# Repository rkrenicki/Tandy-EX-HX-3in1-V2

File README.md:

# Tandy 1000 EX/HX 3-in-1 Expansion Board V2.0

This is a single expansion board designed for the Tandy 1000 EX and HX computers, to include the following upgrades:

* 640KB Base System Memory and 96KB Upper Memory
* 2x 16550-based DE9 Serial RS232 Ports and 1x Parallel Port
* XT-IDE based CompactFlash "Hard Drive"

## Prerequisites

This board is for the Tandy 1000EX and 1000HX computers only.  It will not work in any other computer model as it is.
You must remove any expansion cards already in the computer, this is designed to be a single-board upgrade and has no provisions to allow for any other expansion cards.

## Installing

This board plugs into the Tandy PLUS interface, and takes up all three slots on the rear of the computer.  Please be careful to align the PLUS bus connector before pushing down, to avoid bending pins on the computer.  Secure the backplate to the computer with two screws.
The IDE BIOS will automatically start and boot directly to the CF card on 1000EX machines.   1000HX loads a boot menu by default, and you will need to press F4 to load the IDE BIOS.  If you want to bypass the Tandy DOS ROM and boot menu, run "SETUPHX" and change the "Primary Start-up Device" to "DISK" and press F1 to save.

## Technical Details

This board has no configuration jumpers and is designed to be plug-and-play.  The only jumper is to enable programming the ROM.  Install the jumper to flash the XT-IDE BIOS, otherwise the jumper should be removed.  All assembled boards sold by me come with a pre-programmed ROM, and this jumper should be left empty unless reprogramming to the NEC V20 version of the BIOS, and should be removed immediately after flashing.

The board is hardwired with these memory locations/ports:
```
SRAM:  0x0000-0x5FFF, 0xC800-0xDFFF
UART1: 0x3F8, IRQ 4
UART1: 0x2F8, IRQ 3
LPT2:  0x278, IRQ 2
IDE:   0x300
ROM:   0xC000-0xC7FF
```

## Assembly Notes
All functions of the board are independent, no parts are shared between functions.  If you do not want to use a specific function, you can safely omit any parts referenced with the function in the name (such as "IO" for The MultiIO).

Recommended assembly order: (Shortest to tallest)  **NEEDS UPDATING FOR V2**
* 1  - Resistors (R1-R3)
* 2  - Bypass Capacitors (C1-C16, only noted as "0.1uF" on the boards)
* 3  - 74 series Chips (U1-4, U6-7, U9, U11-13)
* 4  - ROM Socket (U5 Socket)
* 5  - SRAM Chip (U10)
* 6  - Oscillator (OSC1)
* 7  - UART Socket (U8 Socket)  - Pay very special attention to the orientation!  See note below.
* 8  - Connectors (BUS1, CF-J1, CF-J2, 232-P2)
* 9 -  ROM and UART chips into their sockets.
* 10  - CF Adapter
* 11 - Backplate

NOTE:  Please take careful note of part orientation.  To optimize some trace routing, not all chips are oriented in the same direction.  Installing these backwards will destroy the chips.   Pay special attention to IO-U1's socket, it must be installed with the "Pin 1 Arrow" installed facing down with respect to the text on the board.  IO-OSC1 is installed at "9 o'clock", with the squared corner facing the upper left.

## Bill of Materials
  **NEEDS UPDATING FOR V2**
|Quantity |Ref(s)        |Mouser Part Number  |Description                                                     
|-----|----------------|--------------------|----------------------------------------------------------------
| 1   |BUS1            |200-CES13101SD<br><i><b>See Note2 Below</i>|2x31 2.54mm Header Socket
| 1   |CF-J1           |517-8540-4500PL<br><i><b>See Note2 Below</i>|2x20 2.54mm Header Socket, 11mm height.
| 3   |R1 through R3   |603-CFR25SJT-26-10K |10kOhm Resistor
| 12  |C1 through C12  |594-K104M15X7RF53L2 |0.1uF Multilayer Ceramic Capacitor, 2.5mm Lead Spacing
| 1   |CP1             |647-RNU1C101MDS1    |100uF 16V Polymer or Electrolytic Capacitor, 2.5mm Lead Spacing
| 1   |IO-OSC1         |774-MXO45HS-3C-1.8  |1.8432Mhz 1/2-size Oscillator
| 2   |IO-COM1, IO-COM2|806-K22X-E9P-N-99   |DE9 Male Right Angle Connector  
| 4   |IO-COMx Screw   |636-SFSO4401NR      |Jackscrew for DE9 connector
| 1   |IO-U1           |595-TL16C552FNR     |16C552 Dual UART in PLCC-68 Package 
| 1   |IO-U1 Socket    |575-682444          |PLCC-68 Through Hole Socket
| 2   |IO-U2, IO-U3    |595-GD75232N        |GD75232N RS232 Driver
| 1   |IO-U9           |595-SN74LS138N      |74LS138 3-to-8 Line Demux
| 1   |IO-U10          |595-SN74LS08N       |74LS08 Quad AND Gate
| 1   |IO-U11          |595-SN74LS04N       |74LS04 Hex Inverter
| 1   |CF-J2           |200-CES10101TD      |1x2 2.54mm Header Socket
| 1   |CF-U1           |595-SN74LS139AN     |74LS139 Dual 2-to-4 Demux
| 2   |CF-U2, ROM-U4   |595-SN74LS688N<br> or 595-SN74F521N      |74LS688 or 74F521 8-bit Comparator
| 1   |CF-U3           |595-SN74LS245N      |74LS245 Tri-state Bus Transciever
| 1   |RAM-U6          |913-AS6C4008-55PCN  |AS6C4008-55PCN 4mbit (512k x 8) Static RAM
| 1   |RAM-U8          |595-SN74LS00N       |74LS00 Quad NAND Gate
| 1   |RAM-U7          |595-SN74LS32N       |74LS32 Quad OR Gate
| 1   |ROM-U5          |804-39SF010A7CPHE   |39SF010 128k x 8 NOR Flash
| 1   |ROM-U5 Socket   |517-4832-6000-CP    |32-pin Wide DIP Socket
| 1   |CF-IDE Adapter  |n/a                 |CF to IDE Adapter from eBay or AliExpress (See note below)
| 1   |J1              |534-7327            |Mounting Tab for Backplate

Note:	All 74LSxx series logic ICs can be substituted with any family with "LS" or "T" in the name, such as ALS, ACT, AHCT, or HCT among others.

Note2: For the BUS1 Connectors, I have many of these left over from my last order of custom connectors.   You can buy them from me for $1/ea plus shipping.  Even for one, it is far cheaper than the $13 that Mouser wants.   
For small quantities (1-20 connectors), visit my Tindie store to order:  https://www.tindie.com/products/rkrenicki/tandy-1000-ex-and-hx-bus-connector/
For larger quantities, please email tandy.3in1@gmail.com.

## BIOS
  **NEEDS UPDATING FOR V2**
This board uses the XT-IDE Universal BIOS.  I have included pre-configured images for 2.0.0B3 r602 (latest version as of the time of writing this).  The 3in1BIOS-8088.zip will work on any EX or HX computer, and is the version that I preload on assembled boards and kits.   I have also included a V20 Enhanced version for any EX/HX that has an NEC V20 (or clone) installed.   This enhanced version will roughly double your disk speed, but only works on V20 machines.

## CF-IDE Adapter

This board is designed a specific version of a CF-IDE adapter.  They are widely available on eBay and AliExpress.  It bears the mark of "IDE to CF Ver.D2".  It can generally be identified by the metal cover over the CF card connector.   I do not have a link to any one specific vendor or listing, but if the adapter includes the metal backplate and has a metal cover over the CF slot, then it should be correct. 

The CF adapter does also need a few modifications, please refer to the "IDE Adapter Modifications.pdf" for details.  It also has photos of the adapter for reference to buy the proper adapter.

If you have any questions, feel free to join the Discord server below and ask in the #tandy-3in1-support channel.

## Support Discord

I have started a Discord server for more real-time technical support, as well as discussion for my various projects in progress.   You can follow this link to join:  https://discord.gg/QmFssyXnQt

## Built With

* [KiCAD EDA](http://www.kicad.org/)

## Authors

* **Rob Krenicki** - [rkrenicki](https://github.com/rkrenicki)

## License

This project is licensed under the Creative Commons - Attribution - ShareAlike 3.0 License

## Attribution

This board was derrived from works by, uses design elements from, or contains sofware writen by the following:
* Sergey Kiselev (http://www.malinov.com/Home/sergeys-projects)
* James Pearce (https://www.lo-tech.co.uk/)
* Adrian Black (https://www.youtube.com/user/craig1black/featured)
* Jacob Dorne of Monotech PCs (https://monotech.fwscart.com/)
* XTIDE Universal BIOS Team (http://www.xtideuniversalbios.org/)

## README TO-DO
* Assembly Instructions

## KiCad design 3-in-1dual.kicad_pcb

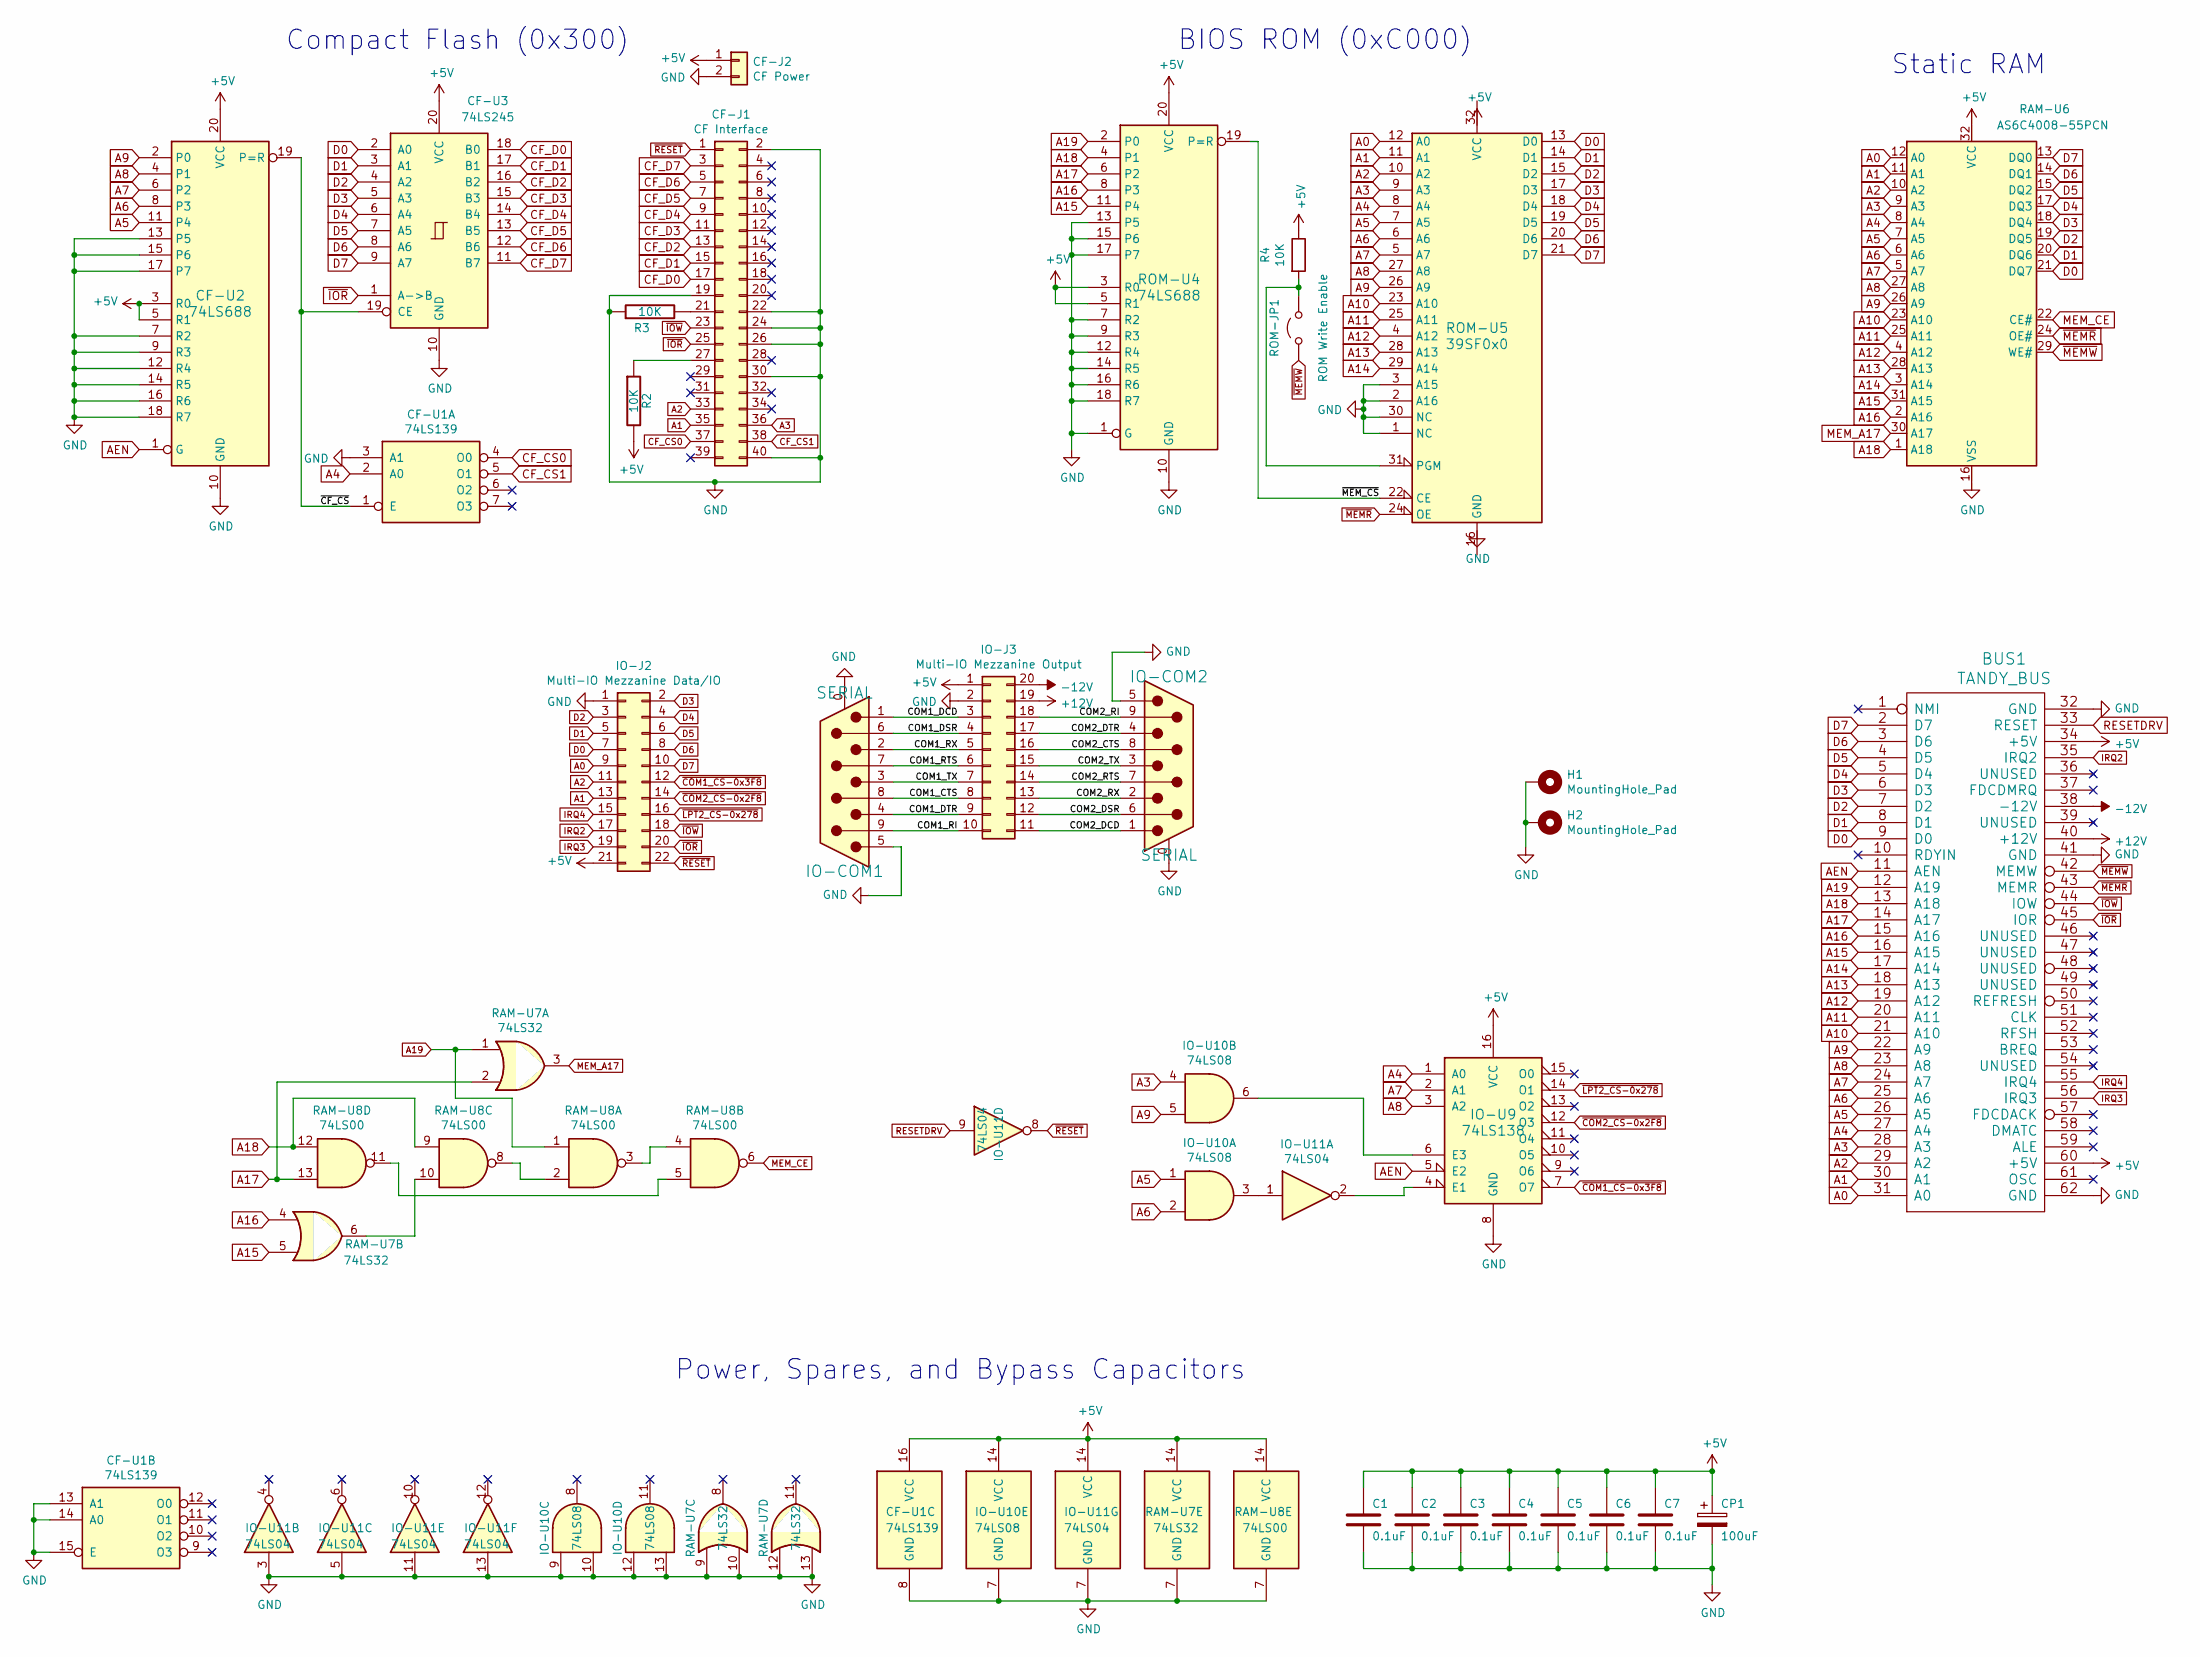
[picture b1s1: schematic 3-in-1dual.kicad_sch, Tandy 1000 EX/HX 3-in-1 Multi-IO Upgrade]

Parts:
BUS1: TANDY_BUS; TANDY-PLUS-BUS
C1, C2, C3, C4, C5, C6, C7: 0.1uF; C_Disc_D3.0mm_W2.0mm_P2.50mm
CF-J1: CF Interface; PinSocket_2x20_P2.54mm_Vertical
CF-J2: CF Power; PinSocket_1x02_P2.54mm_Vertical
CF-U1: 74LS139; DIP-16_W7.62mm
CF-U2: 74LS688; DIP-20_W7.62mm
CF-U3: 74LS245; DIP-20_W7.62mm
CP1: 100uF; CP_Radial_D5.0mm_P2.50mm
H1, H2: MountingHole_Pad; MountingHole_2.7mm_M2.5_ISO14580_Pad
IO-COM1, IO-COM2: SERIAL; DSUB-9_Male_Horizontal_P2.77x2.84mm_EdgePinOffset7.70mm_Hou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
IO-J2: Multi-IO Mezzanine Data/IO; PinHeader_2x11_P2.54mm_Vertical
IO-J3: Multi-IO Mezzanine Output; PinHeader_2x10_P2.54mm_Vertical
IO-U9: 74LS138; DIP-16_W7.62mm
IO-U10: 74LS08; DIP-14_W7.62mm
IO-U11: 74LS04; DIP-14_W7.62mm
R2, R3, R4: 10K; R_Axial_DIN0204_L3.6mm_D1.6mm_P5.08mm_Horizontal
RAM-U6: AS6C4008-55PCN; DIP-32_W15.24mm
RAM-U7: 74LS32; DIP-14_W7.62mm
RAM-U8: 74LS00; DIP-14_W7.62mm
ROM-JP1: ROM Write Enable; PinHeader_1x02_P2.54mm_Vertical
ROM-U4: 74LS688; DIP-20_W7.62mm
ROM-U5: 39SF0x0; DIP-32_W15.24mm

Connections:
+5V: BUS1.34 (+5V), BUS1.60 (+5V), C1.1, C2.1, C3.1, C4.1, C5.1, C6.1, C7.1, CF-J2.1, CF-U1.16 (VCC), CF-U2.3 (R0), CF-U2.5 (R1), CF-U2.20 (VCC), CF-U3.20 (VCC), CP1.1, IO-J2.21, IO-J3.1, IO-U9.16 (VCC), IO-U10.14 (VCC), IO-U11.14 (VCC), R2.2, R4.1, RAM-U6.32 (VCC), RAM-U7.14 (VCC), RAM-U8.14 (VCC), ROM-U4.3 (R0), ROM-U4.5 (R1), ROM-U4.20 (VCC), ROM-U5.32 (VCC)
+12V: BUS1.40 (+12V), IO-J3.19
-12V: BUS1.38 (-12V), IO-J3.20
/COM1_CTS: IO-COM1.8, IO-J3.8
/COM1_DCD: IO-COM1.1, IO-J3.3
/COM1_DSR: IO-COM1.6, IO-J3.4
/COM1_DTR: IO-COM1.4, IO-J3.9
/COM1_RI: IO-COM1.9, IO-J3.10
/COM1_RTS: IO-COM1.7, IO-J3.6
/COM1_RX: IO-COM1.2, IO-J3.5
/COM1_TX: IO-COM1.3, IO-J3.7
/COM2_CTS: IO-COM2.8, IO-J3.16
/COM2_DCD: IO-COM2.1, IO-J3.11
/COM2_DSR: IO-COM2.6, IO-J3.12
/COM2_DTR: IO-COM2.4, IO-J3.17
/COM2_RI: IO-COM2.9, IO-J3.18
/COM2_RTS: IO-COM2.7, IO-J3.14
/COM2_RX: IO-COM2.2, IO-J3.13
/COM2_TX: IO-COM2.3, IO-J3.15
/~CF_CS: CF-U1.1 (E), CF-U2.19 (P=R), CF-U3.19 (CE)
/~MEM_CS: ROM-U4.19 (P=R), ROM-U5.22 (CE)
A0: BUS1.31 (A0), IO-J2.9, RAM-U6.12 (A0), ROM-U5.12 (A0)
A1: BUS1.30 (A1), CF-J1.35, IO-J2.13, RAM-U6.11 (A1), ROM-U5.11 (A1)
A2: BUS1.29 (A2), CF-J1.33, IO-J2.11, RAM-U6.10 (A2), ROM-U5.10 (A2)
A3: BUS1.28 (A3), CF-J1.36, IO-U10.4, RAM-U6.9 (A3), ROM-U5.9 (A3)
A4: BUS1.27 (A4), CF-U1.2 (A0), IO-U9.1 (A0), RAM-U6.8 (A4), ROM-U5.8 (A4)
A5: BUS1.26 (A5), CF-U2.11 (P4), IO-U10.1, RAM-U6.7 (A5), ROM-U5.7 (A5)
A6: BUS1.25 (A6), CF-U2.8 (P3), IO-U10.2, RAM-U6.6 (A6), ROM-U5.6 (A6)
A7: BUS1.24 (A7), CF-U2.6 (P2), IO-U9.2 (A1), RAM-U6.5 (A7), ROM-U5.5 (A7)
A8: BUS1.23 (A8), CF-U2.4 (P1), IO-U9.3 (A2), RAM-U6.27 (A8), ROM-U5.27 (A8)
A9: BUS1.22 (A9), CF-U2.2 (P0), IO-U10.5, RAM-U6.26 (A9), ROM-U5.26 (A9)
A10: BUS1.21 (A10), RAM-U6.23 (A10), ROM-U5.23 (A10)
A11: BUS1.20 (A11), RAM-U6.25 (A11), ROM-U5.25 (A11)
A12: BUS1.19 (A12), RAM-U6.4 (A12), ROM-U5.4 (A12)
A13: BUS1.18 (A13), RAM-U6.28 (A13), ROM-U5.28 (A13)
A14: BUS1.17 (A14), RAM-U6.3 (A14), ROM-U5.29 (A14)
A15: BUS1.16 (A15), RAM-U6.31 (A15), RAM-U7.5, ROM-U4.11 (P4)
A16: BUS1.15 (A16), RAM-U6.2 (A16), RAM-U7.4, ROM-U4.8 (P3)
A17: BUS1.14 (A17), RAM-U7.2, RAM-U8.13, ROM-U4.6 (P2)
A18: BUS1.13 (A18), RAM-U6.1 (A18), RAM-U8.9, RAM-U8.12, ROM-U4.4 (P1)
A19: BUS1.12 (A19), RAM-U7.1, RAM-U8.1, ROM-U4.2 (P0)
AEN: BUS1.11 (AEN), CF-U2.1 (G), IO-U9.5 (E2)
CF_CS0: CF-J1.37, CF-U1.4 (O0)
CF_CS1: CF-J1.38, CF-U1.5 (O1)
CF_D0: CF-J1.17, CF-U3.18 (B0)
CF_D1: CF-J1.15, CF-U3.17 (B1)
CF_D2: CF-J1.13, CF-U3.16 (B2)
CF_D3: CF-J1.11, CF-U3.15 (B3)
CF_D4: CF-J1.9, CF-U3.14 (B4)
CF_D5: CF-J1.7, CF-U3.13 (B5)
CF_D6: CF-J1.5, CF-U3.12 (B6)
CF_D7: CF-J1.3, CF-U3.11 (B7)
D0: BUS1.9 (D0), CF-U3.2 (A0), IO-J2.7, RAM-U6.21 (DQ7), ROM-U5.13 (D0)
D1: BUS1.8 (D1), CF-U3.3 (A1), IO-J2.5, RAM-U6.20 (DQ6), ROM-U5.14 (D1)
D2: BUS1.7 (D2), CF-U3.4 (A2), IO-J2.3, RAM-U6.19 (DQ5), ROM-U5.15 (D2)
D3: BUS1.6 (D3), CF-U3.5 (A3), IO-J2.2, RAM-U6.18 (DQ4), ROM-U5.17 (D3)
D4: BUS1.5 (D4), CF-U3.6 (A4), IO-J2.4, RAM-U6.17 (DQ3), ROM-U5.18 (D4)
D5: BUS1.4 (D5), CF-U3.7 (A5), IO-J2.6, RAM-U6.15 (DQ2), ROM-U5.19 (D5)
D6: BUS1.3 (D6), CF-U3.8 (A6), IO-J2.8, RAM-U6.14 (DQ1), ROM-U5.20 (D6)
D7: BUS1.2 (D7), CF-U3.9 (A7), IO-J2.10, RAM-U6.13 (DQ0), ROM-U5.21 (D7)
GND: BUS1.32 (GND), BUS1.41 (GND), BUS1.62 (GND), C1.2, C2.2, C3.2, C4.2, C5.2, C6.2, C7.2, CF-J1.2, CF-J1.19, CF-J1.22, CF-J1.24, CF-J1.26, CF-J1.30, CF-J1.40, CF-J2.2, CF-U1.3 (A1), CF-U1.8 (GND), CF-U1.13 (A1), CF-U1.14 (A0), CF-U1.15 (E), CF-U2.7 (R2), CF-U2.9 (R3), CF-U2.10 (GND), CF-U2.12 (R4), CF-U2.13 (P5), CF-U2.14 (R5), CF-U2.15 (P6), CF-U2.16 (R6), CF-U2.17 (P7), CF-U2.18 (R7), CF-U3.10 (GND), CP1.2, H1.1, H2.1, IO-COM1.0 (PAD), IO-COM1.5, IO-COM2.0 (PAD), IO-COM2.5, IO-J2.1, IO-J3.2, IO-U9.8 (GND), IO-U10.7 (GND), IO-U10.9, IO-U10.10, IO-U10.12, IO-U10.13, IO-U11.3, IO-U11.5, IO-U11.7 (GND), IO-U11.11, IO-U11.13, R3.1, RAM-U6.16 (VSS), RAM-U7.7 (GND), RAM-U7.9, RAM-U7.10, RAM-U7.12, RAM-U7.13, RAM-U8.7 (GND), ROM-U4.1 (G), ROM-U4.7 (R2), ROM-U4.9 (R3), ROM-U4.10 (GND), ROM-U4.12 (R4), ROM-U4.13 (P5), ROM-U4.14 (R5), ROM-U4.15 (P6), ROM-U4.16 (R6), ROM-U4.17 (P7), ROM-U4.18 (R7), ROM-U5.1 (NC), ROM-U5.2 (A16), ROM-U5.3 (A15), ROM-U5.16 (GND), ROM-U5.30 (NC)
IRQ2: BUS1.35 (IRQ2), IO-J2.17
IRQ3: BUS1.56 (IRQ3), IO-J2.19
IRQ4: BUS1.55 (IRQ4), IO-J2.15
MEM_A17: RAM-U6.30 (A17), RAM-U7.3
MEM_CE: RAM-U6.22 (CE#), RAM-U8.6
unnamed: CF-J1.21, R3.2
unnamed: CF-J1.27, R2.1
unnamed: IO-U10.3, IO-U11.1
unnamed: IO-U9.6 (E3), IO-U10.6
unnamed: IO-U9.4 (E1), IO-U11.2
unnamed: R4.2, ROM-JP1.2 (B), ROM-U5.31 (PGM)
unnamed: RAM-U7.6, RAM-U8.10
unnamed: RAM-U8.2, RAM-U8.8
unnamed: RAM-U8.3, RAM-U8.4
unnamed: RAM-U8.5, RAM-U8.11
RESETDRV: BUS1.33 (RESET), IO-U11.9
~COM1_CS-0x3F8: IO-J2.12, IO-U9.7 (O7)
~COM2_CS-0x2F8: IO-J2.14, IO-U9.12 (O3)
~IOR: BUS1.45 (IOR), CF-J1.25, CF-U3.1 (A->B), IO-J2.20
~IOW: BUS1.44 (IOW), CF-J1.23, IO-J2.18
~LPT2_CS-0x278: IO-J2.16, IO-U9.14 (O1)
~MEMR: BUS1.43 (MEMR), RAM-U6.24 (OE#), ROM-U5.24 (OE)
~MEMW: BUS1.42 (MEMW), RAM-U6.29 (WE#), ROM-JP1.1 (A)
~RESET: CF-J1.1, IO-J2.22, IO-U11.8

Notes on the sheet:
Compact Flash (0x300)
Static RAM
BIOS ROM (0xC000)
Power, Spares, and Bypass Capacitors

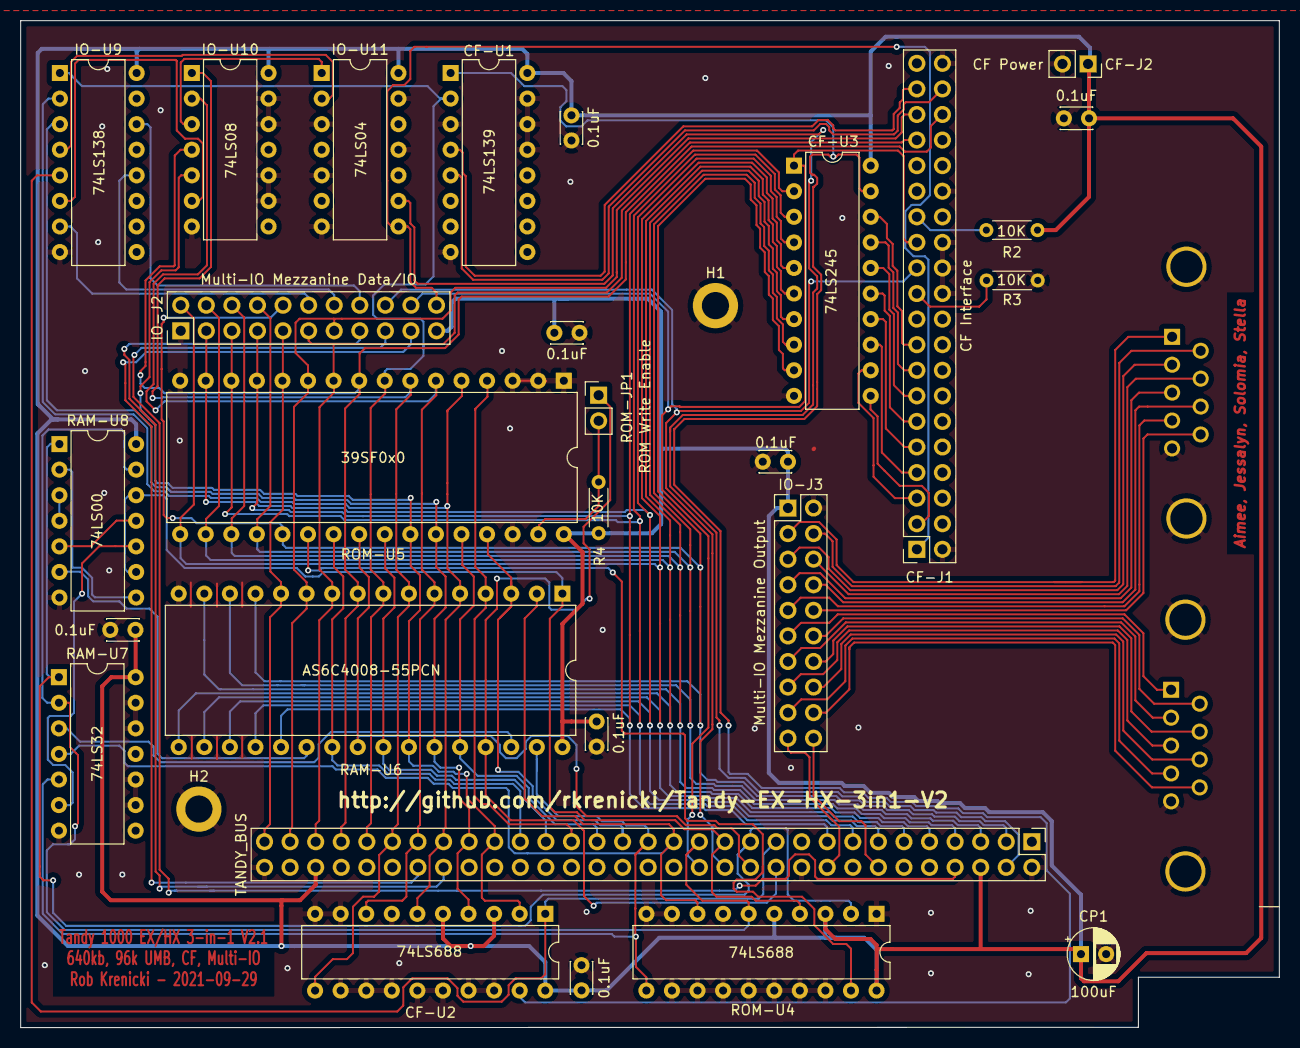
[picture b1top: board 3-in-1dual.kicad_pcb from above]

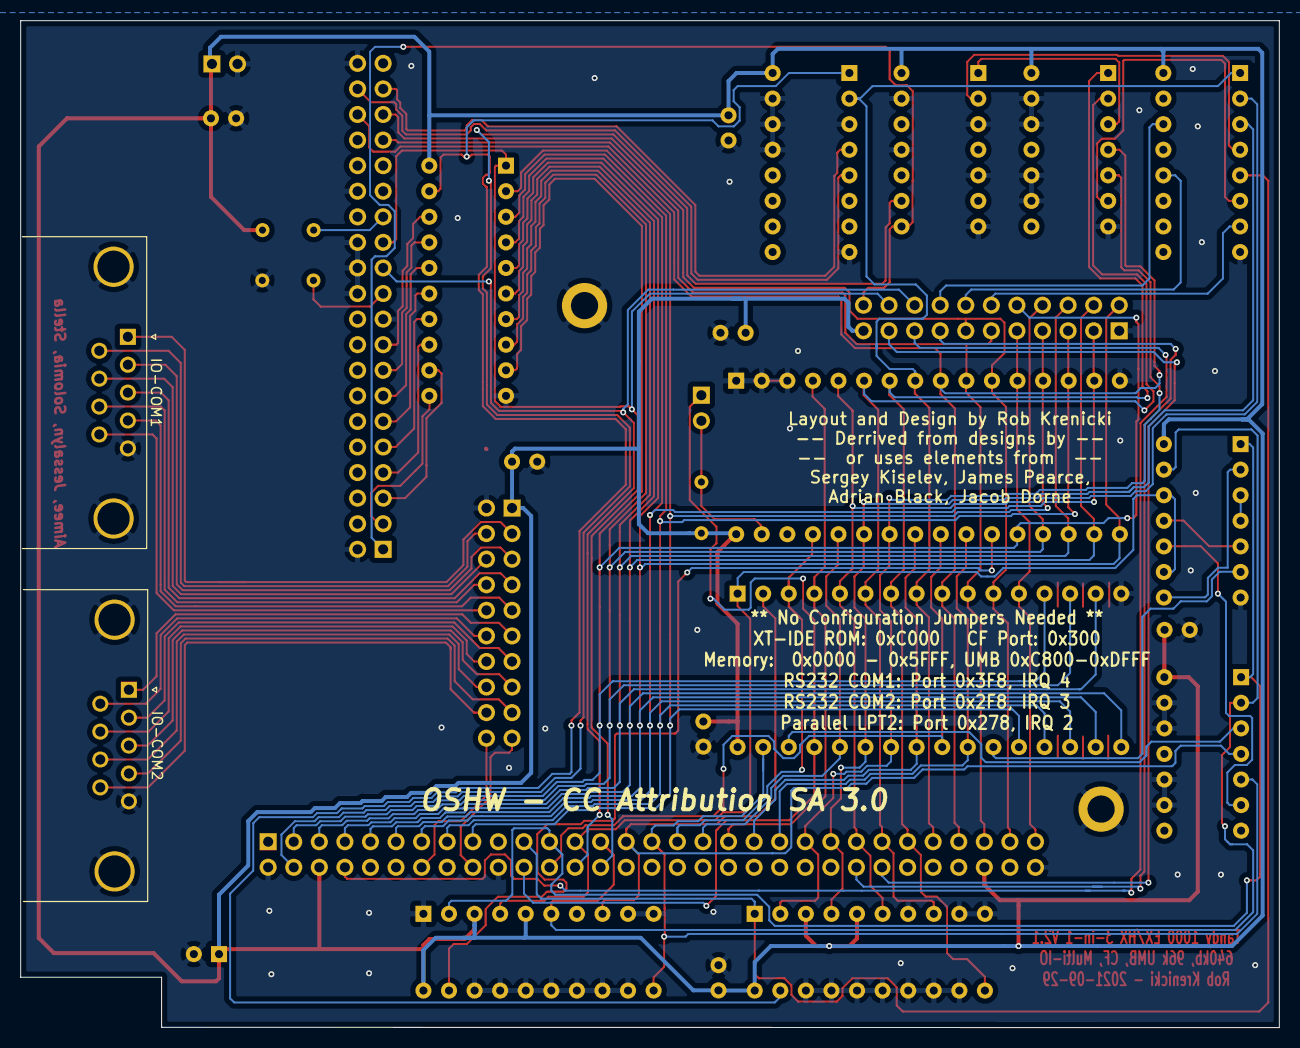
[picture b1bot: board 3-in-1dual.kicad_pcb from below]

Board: 2 copper layers, 125.0 x 100.0 mm, 32 parts (2 on the bottom side), 85 nets.

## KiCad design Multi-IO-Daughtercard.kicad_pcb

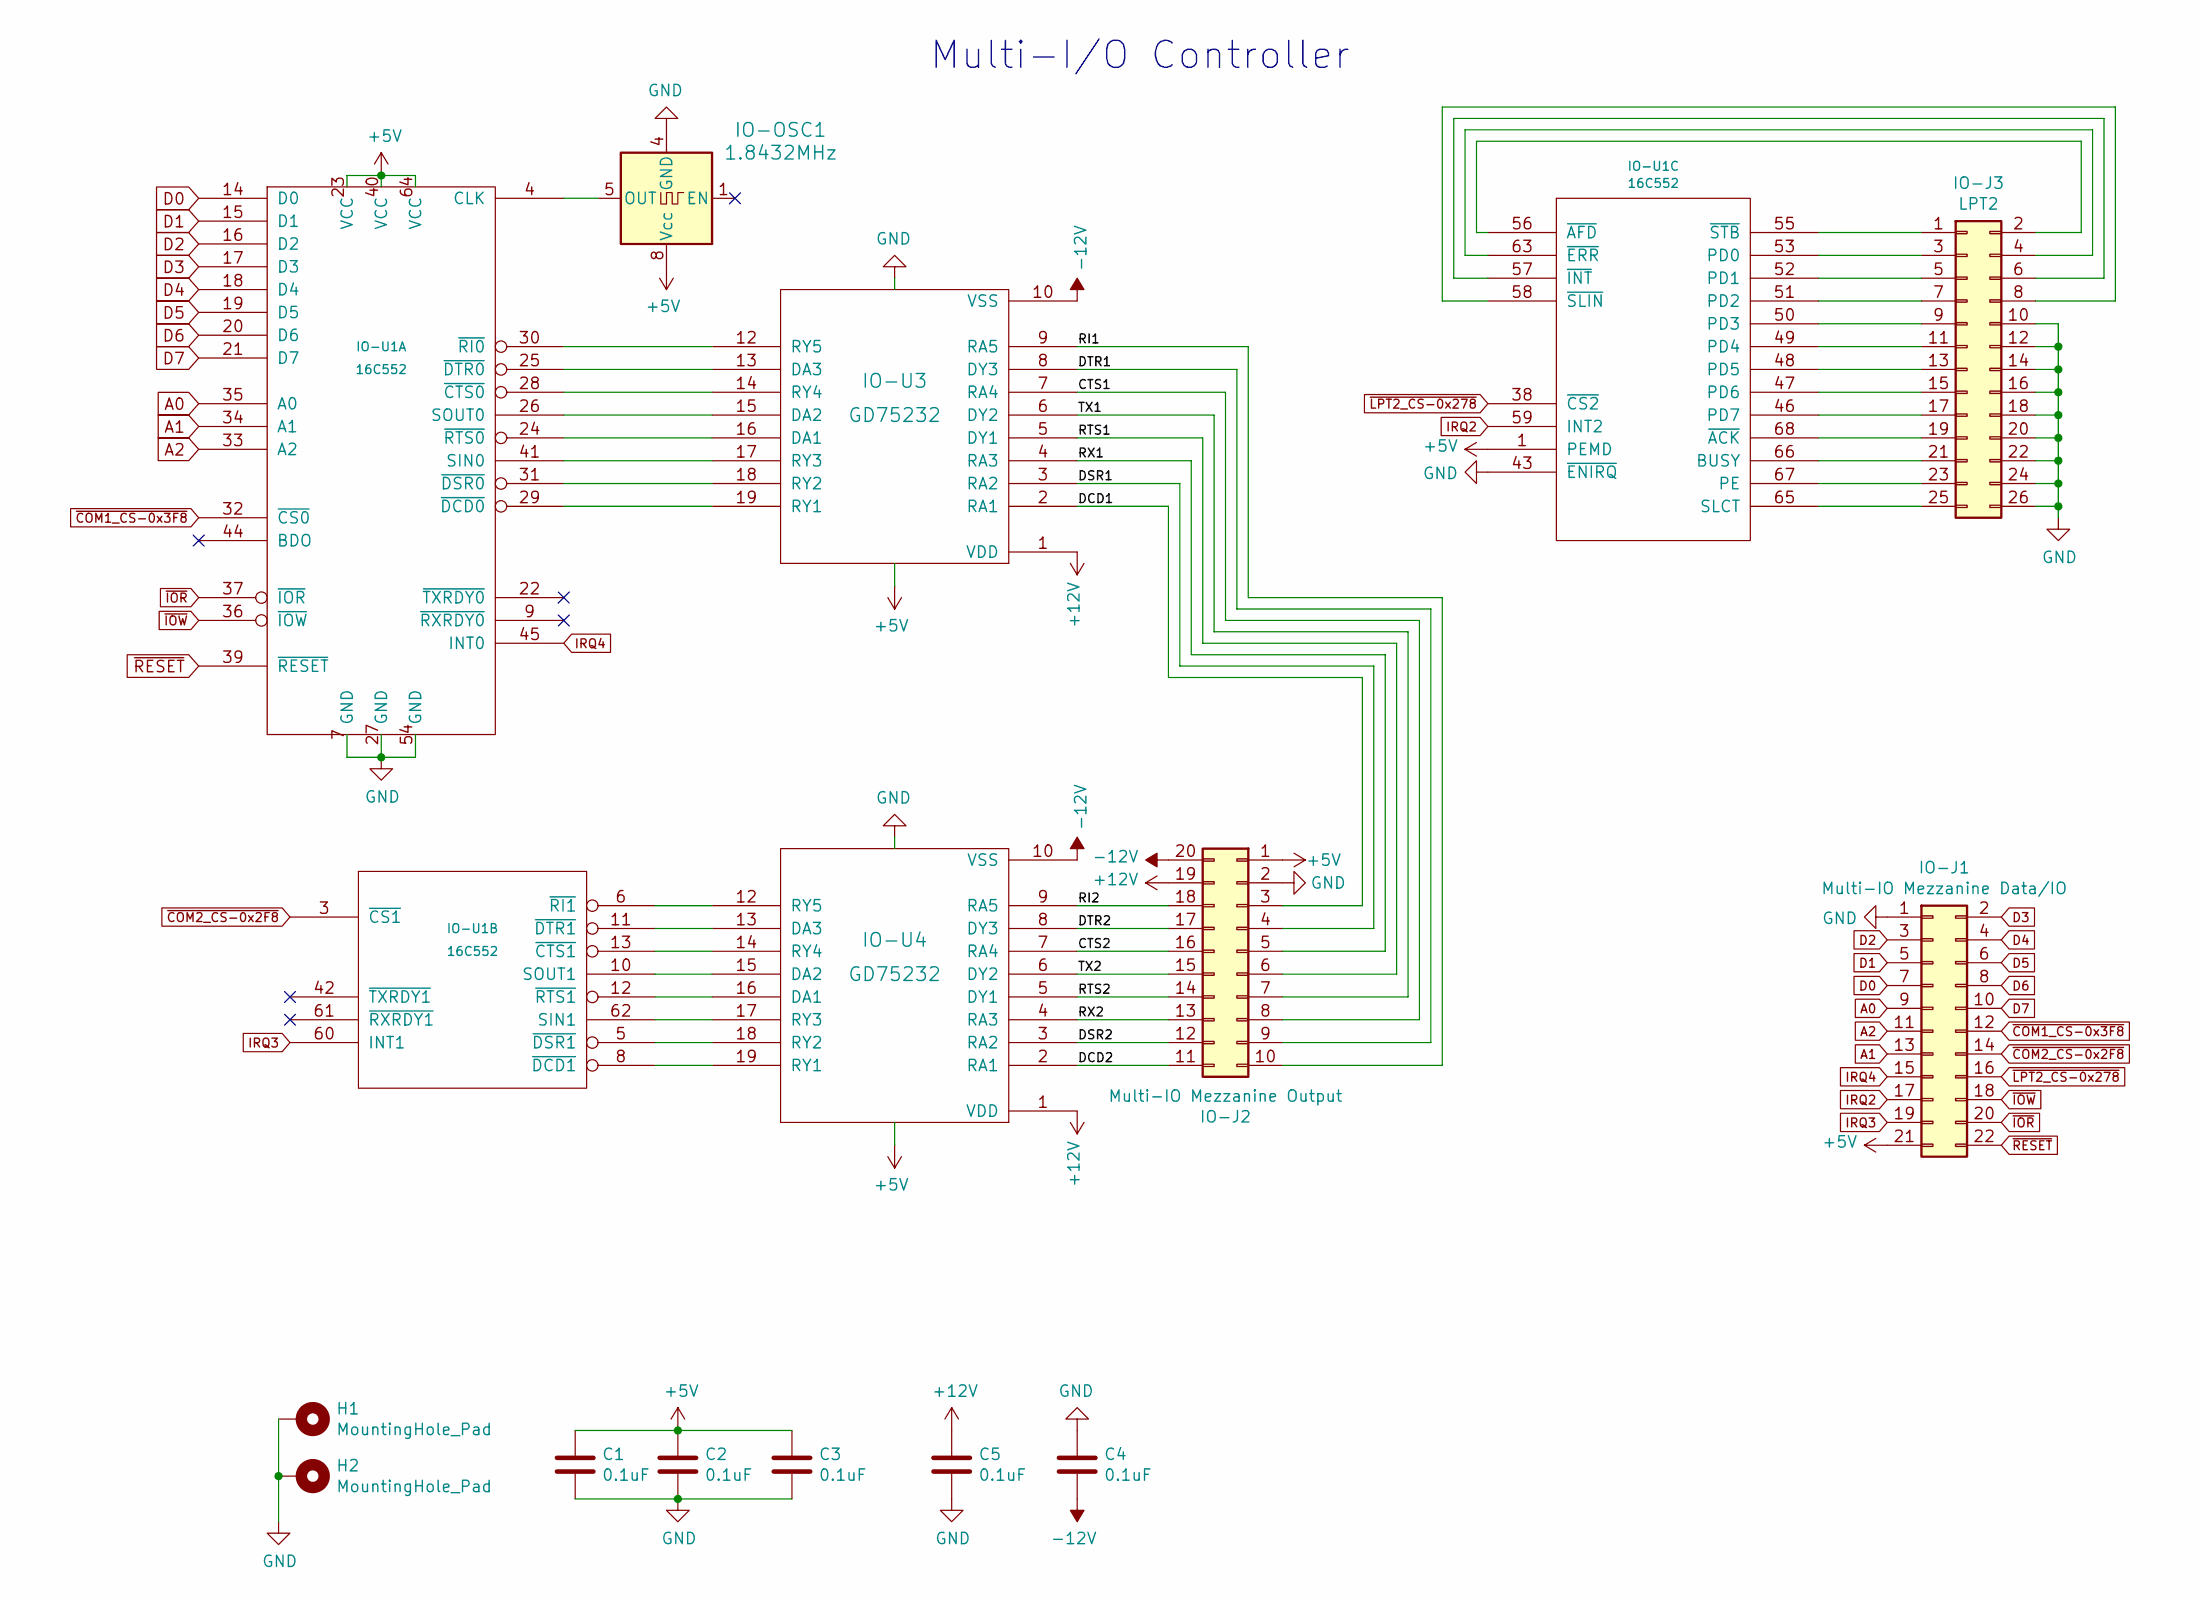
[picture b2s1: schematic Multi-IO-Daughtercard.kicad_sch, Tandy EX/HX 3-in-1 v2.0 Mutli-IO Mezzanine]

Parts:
C1, C2, C3, C4, C5: 0.1uF; C_Disc_D3.0mm_W2.0mm_P2.50mm
H1, H2: MountingHole_Pad; MountingHole_2.7mm_M2.5_ISO14580_Pad
IO-J1: Multi-IO Mezzanine Data/IO; PinSocket_2x11_P2.54mm_Vertical
IO-J2: Multi-IO Mezzanine Output; PinSocket_2x10_P2.54mm_Vertical
IO-J3: LPT2; PinHeader_2x13_P2.54mm_Horizontal
IO-OSC1: 1.8432MHz; Oscillator_DIP-8
IO-U1: 16C552; PLCC-68_THT-Socket
IO-U3, IO-U4: GD75232; DIP-20_W7.62mm

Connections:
+5V: C1.1, C2.1, C3.1, IO-J1.21, IO-J2.1, IO-OSC1.8 (Vcc), IO-U1.1 (PEMD), IO-U1.23 (VCC), IO-U1.40 (VCC), IO-U1.64 (VCC), IO-U3.20 (VCC), IO-U4.20 (VCC)
+12V: C5.1, IO-J2.19, IO-U3.1 (VDD), IO-U4.1 (VDD)
-12V: C4.2, IO-J2.20, IO-U3.10 (VSS), IO-U4.10 (VSS)
/CTS1: IO-J2.8, IO-U3.7 (RA4)
/CTS2: IO-J2.16, IO-U4.7 (RA4)
/DCD1: IO-J2.3, IO-U3.2 (RA1)
/DCD2: IO-J2.11, IO-U4.2 (RA1)
/DSR1: IO-J2.4, IO-U3.3 (RA2)
/DSR2: IO-J2.12, IO-U4.3 (RA2)
/DTR1: IO-J2.9, IO-U3.8 (DY3)
/DTR2: IO-J2.17, IO-U4.8 (DY3)
/RI1: IO-J2.10, IO-U3.9 (RA5)
/RI2: IO-J2.18, IO-U4.9 (RA5)
/RTS1: IO-J2.6, IO-U3.5 (DY1)
/RTS2: IO-J2.14, IO-U4.5 (DY1)
/RX1: IO-J2.5, IO-U3.4 (RA3)
/RX2: IO-J2.13, IO-U4.4 (RA3)
/TX1: IO-J2.7, IO-U3.6 (DY2)
/TX2: IO-J2.15, IO-U4.6 (DY2)
A0: IO-J1.9, IO-U1.35 (A0)
A1: IO-J1.13, IO-U1.34 (A1)
A2: IO-J1.11, IO-U1.33 (A2)
D0: IO-J1.7, IO-U1.14 (D0)
D1: IO-J1.5, IO-U1.15 (D1)
D2: IO-J1.3, IO-U1.16 (D2)
D3: IO-J1.2, IO-U1.17 (D3)
D4: IO-J1.4, IO-U1.18 (D4)
D5: IO-J1.6, IO-U1.19 (D5)
D6: IO-J1.8, IO-U1.20 (D6)
D7: IO-J1.10, IO-U1.21 (D7)
GND: C1.2, C2.2, C3.2, C4.1, C5.2, H1.1, H2.1, IO-J1.1, IO-J2.2, IO-J3.10, IO-J3.12, IO-J3.14, IO-J3.16, IO-J3.18, IO-J3.20, IO-J3.22, IO-J3.24, IO-J3.26, IO-OSC1.4 (GND), IO-U1.7 (GND), IO-U1.27 (GND), IO-U1.43 (~ENIRQ), IO-U1.54 (GND), IO-U3.11 (GND), IO-U4.11 (GND)
IRQ2: IO-J1.17, IO-U1.59 (INT2)
IRQ3: IO-J1.19, IO-U1.60 (INT1)
IRQ4: IO-J1.15, IO-U1.45 (INT0)
unnamed: IO-J3.1, IO-U1.55 (~STB)
unnamed: IO-J3.2, IO-U1.56 (~AFD)
unnamed: IO-J3.3, IO-U1.53 (PD0)
unnamed: IO-J3.4, IO-U1.63 (~ERR)
unnamed: IO-J3.5, IO-U1.52 (PD1)
unnamed: IO-J3.6, IO-U1.57 (~INT)
unnamed: IO-J3.7, IO-U1.51 (PD2)
unnamed: IO-J3.8, IO-U1.58 (~SLIN)
unnamed: IO-J3.9, IO-U1.50 (PD3)
unnamed: IO-J3.11, IO-U1.49 (PD4)
unnamed: IO-J3.13, IO-U1.48 (PD5)
unnamed: IO-J3.15, IO-U1.47 (PD6)
unnamed: IO-J3.17, IO-U1.46 (PD7)
unnamed: IO-J3.19, IO-U1.68 (~ACK)
unnamed: IO-J3.21, IO-U1.66 (BUSY)
unnamed: IO-J3.23, IO-U1.67 (PE)
unnamed: IO-J3.25, IO-U1.65 (SLCT)
unnamed: IO-OSC1.5 (OUT), IO-U1.4 (CLK)
unnamed: IO-U1.5 (~DSR1), IO-U4.18 (RY2)
unnamed: IO-U1.6 (~RI1), IO-U4.12 (RY5)
unnamed: IO-U1.8 (~DCD1), IO-U4.19 (RY1)
unnamed: IO-U1.10 (SOUT1), IO-U4.15 (DA2)
unnamed: IO-U1.11 (~DTR1), IO-U4.13 (DA3)
unnamed: IO-U1.12 (~RTS1), IO-U4.16 (DA1)
unnamed: IO-U1.13 (~CTS1), IO-U4.14 (RY4)
unnamed: IO-U1.24 (~RTS0), IO-U3.16 (DA1)
unnamed: IO-U1.25 (~DTR0), IO-U3.13 (DA3)
unnamed: IO-U1.26 (SOUT0), IO-U3.15 (DA2)
unnamed: IO-U1.28 (~CTS0), IO-U3.14 (RY4)
unnamed: IO-U1.29 (~DCD0), IO-U3.19 (RY1)
unnamed: IO-U1.30 (~RI0), IO-U3.12 (RY5)
unnamed: IO-U1.31 (~DSR0), IO-U3.18 (RY2)
unnamed: IO-U1.41 (SIN0), IO-U3.17 (RY3)
unnamed: IO-U1.62 (SIN1), IO-U4.17 (RY3)
~COM1_CS-0x3F8: IO-J1.12, IO-U1.32 (~CS0)
~COM2_CS-0x2F8: IO-J1.14, IO-U1.3 (~CS1)
~IOR: IO-J1.20, IO-U1.37 (~IOR)
~IOW: IO-J1.18, IO-U1.36 (~IOW)
~LPT2_CS-0x278: IO-J1.16, IO-U1.38 (~CS2)
~RESET: IO-J1.22, IO-U1.39 (~RESET)

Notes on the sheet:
Multi-I/O Controller

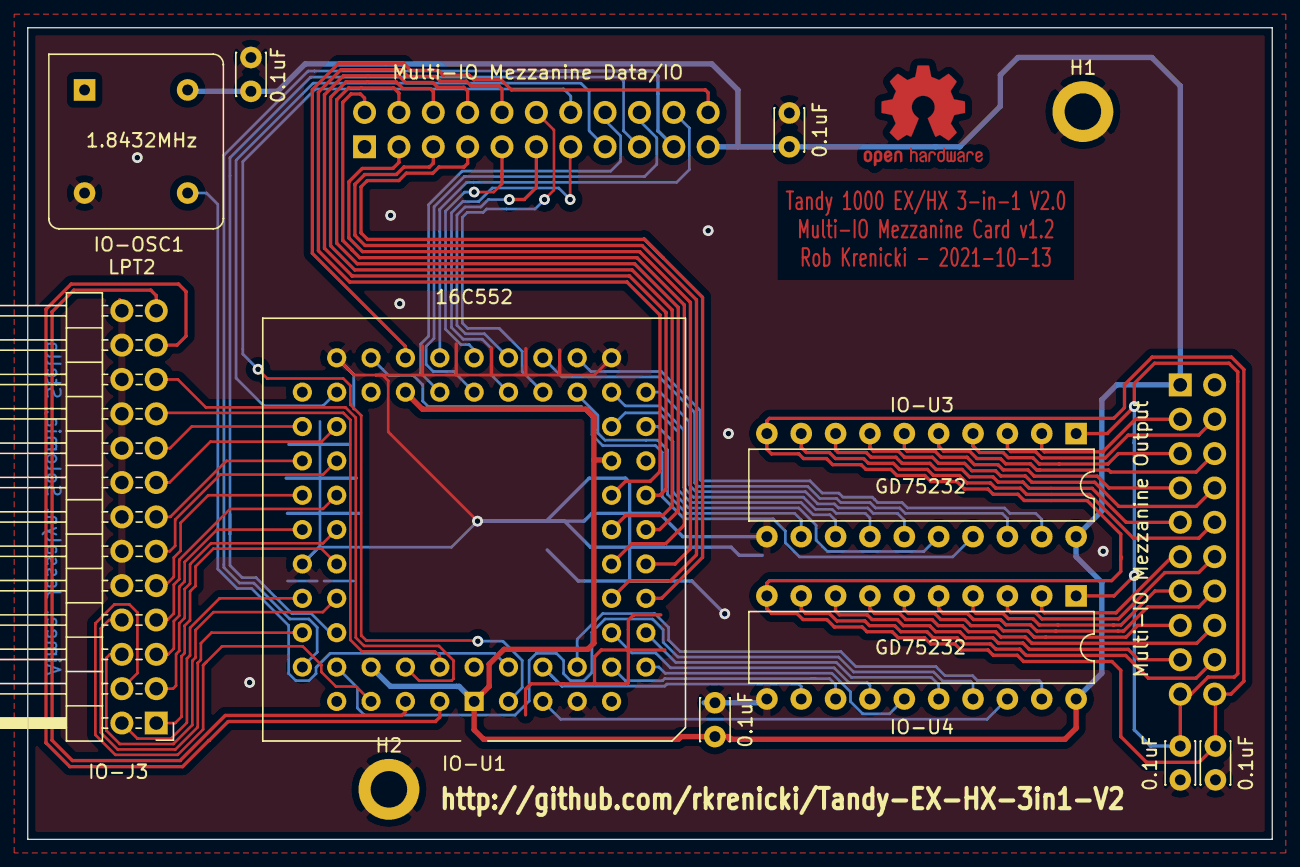
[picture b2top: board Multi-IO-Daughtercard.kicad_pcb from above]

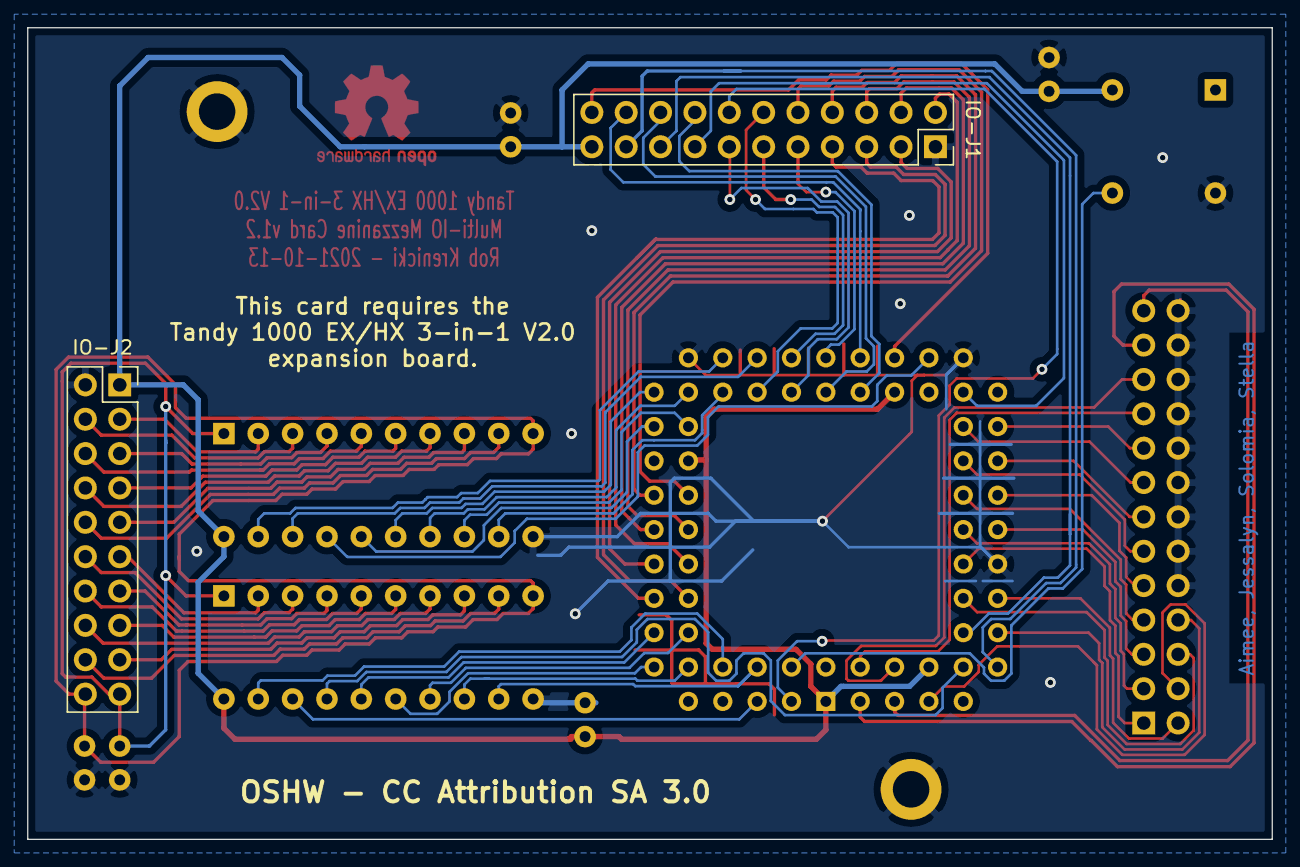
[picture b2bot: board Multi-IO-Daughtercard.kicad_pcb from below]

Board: 2 copper layers, 92.0 x 60.0 mm, 14 parts (2 on the bottom side), 74 nets.

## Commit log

2021-11-09 Update README.md
    Partial correction for V2.0 boards
2023-01-08 Add Drivers, BIOS, and Flash utility.
2025-11-08 Update to KiCAD 9

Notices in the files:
3-in-1dual.kicad_sch:
OSHW - Creative Commons Attribution ShareAlike 3.0
